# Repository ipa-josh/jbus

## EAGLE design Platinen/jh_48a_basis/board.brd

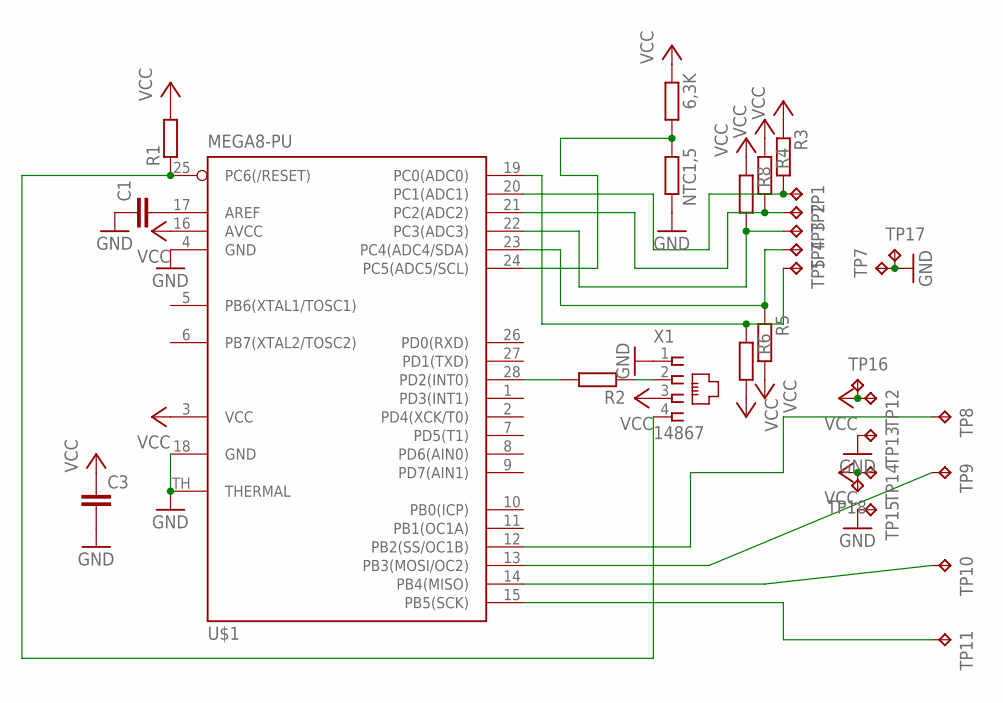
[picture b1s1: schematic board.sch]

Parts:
6,3K: R-EU_R0805; R0805
C1, C3: C-EUC0805; C0805
NTC1,5: R-EU_0207/7; 0207/7
R1, R2, R3, R4, R5, R6, R8: R-EU_R0805; R0805
TP1, TP2, TP3, TP4, TP5, TP7, TP8, TP9, TP10, TP11, TP12, TP13, TP14, TP15, TP16, TP17, TP18: TPPAD1-13; P1-13
U$1: MEGA8-PU; MLF28-TH
X1: 14867

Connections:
GND: C1.1, C3.2, NTC1,5.2, TP7.TP, TP13.TP, TP15.TP, TP17.TP, U$1.4 (GND), U$1.18 (GND), U$1.TH (THERMAL), X1.1
unnamed: R2.2, U$1.28 (PD2(INT0))
unnamed: R1.1, U$1.25 (PC6(/RESET)), X1.4
unnamed: TP8.TP, U$1.12 (PB2(SS/OC1B))
unnamed: TP10.TP, U$1.14 (PB4(MISO))
unnamed: C1.2, U$1.17 (AREF)
unnamed: TP9.TP, U$1.13 (PB3(MOSI/OC2))
unnamed: R8.2, TP3.TP, U$1.22 (PC3(ADC3))
unnamed: R3.2, TP1.TP, U$1.20 (PC1(ADC1))
unnamed: R5.1, TP4.TP, U$1.23 (PC4(ADC4/SDA))
unnamed: R6.1, TP5.TP, U$1.19 (PC0(ADC0))
unnamed: 6,3K.2, NTC1,5.1, U$1.24 (PC5(ADC5/SCL))
unnamed: R2.1, X1.2
unnamed: TP11.TP, U$1.15 (PB5(SCK))
unnamed: R4.2, TP2.TP, U$1.21 (PC2(ADC2))
VCC: 6,3K.1, C3.1, R1.2, R3.1, R4.1, R5.2, R6.2, R8.1, TP12.TP, TP14.TP, TP16.TP, TP18.TP, U$1.3 (VCC), U$1.16 (AVCC), X1.3

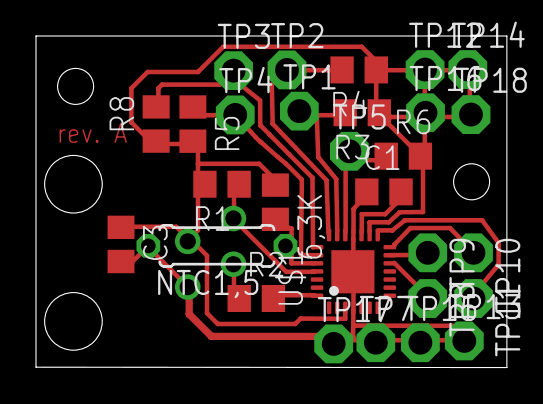
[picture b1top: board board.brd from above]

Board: 2 copper layers, 26.2 x 18.4 mm, 30 parts (1 on the bottom side), 16 nets.

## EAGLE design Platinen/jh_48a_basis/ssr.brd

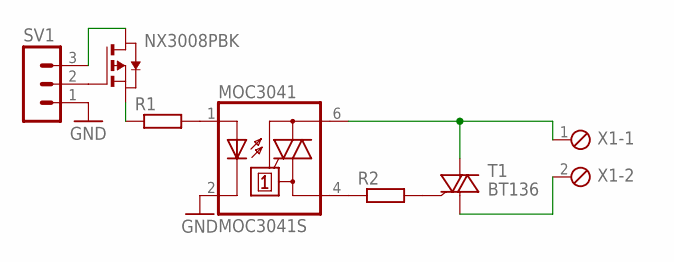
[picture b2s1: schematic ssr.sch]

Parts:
MOC3041: MOC3041S; DIL6-SMD; MPN MOC3041S-M
NX3008PBK: PMOSSOT23; SOT-23
R1, R2: R-EU_R1206; R1206
SV1: MA03-1
T1: BT136; TO220AB
X1: MPT2; 2POL254

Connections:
GND: MOC3041.2 (C), SV1.1
unnamed: MOC3041.1 (A), R1.2
unnamed: NX3008PBK.2 (S), R1.1
unnamed: MOC3041.4 (A1), R2.1
unnamed: R2.2, T1.3 (G)
unnamed: MOC3041.6 (A2), T1.2 (A2), X1.1
unnamed: T1.1 (A1), X1.2
unnamed: NX3008PBK.3 (G), SV1.2
unnamed: NX3008PBK.1 (D), SV1.3

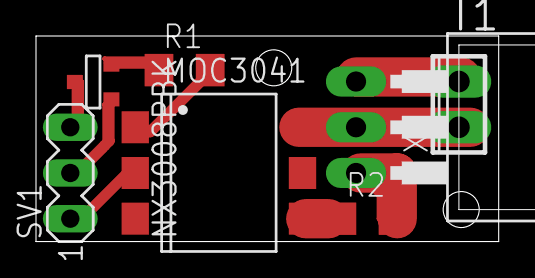
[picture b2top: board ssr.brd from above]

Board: 2 copper layers, 25.7 x 11.4 mm, 7 parts (0 on the bottom side), 9 nets.

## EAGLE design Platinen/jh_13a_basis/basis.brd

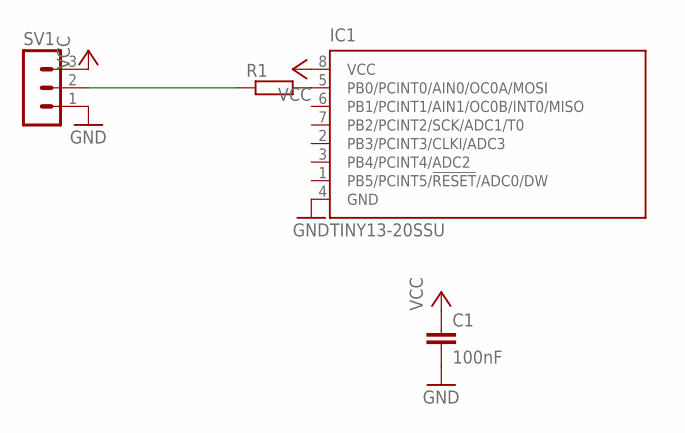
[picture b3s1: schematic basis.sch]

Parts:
C1: 100nF; C0603
IC1: TINY13-20SSU; 8S1
R1: R-EU_R0805; R0805
SV1: MA03-1

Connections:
GND: C1.2, IC1.4 (GND), SV1.1
unnamed: IC1.5 (PB0/PCINT0/AIN0/OC0A/MOSI), R1.2
unnamed: R1.1, SV1.2
VCC: C1.1, IC1.8 (VCC), SV1.3

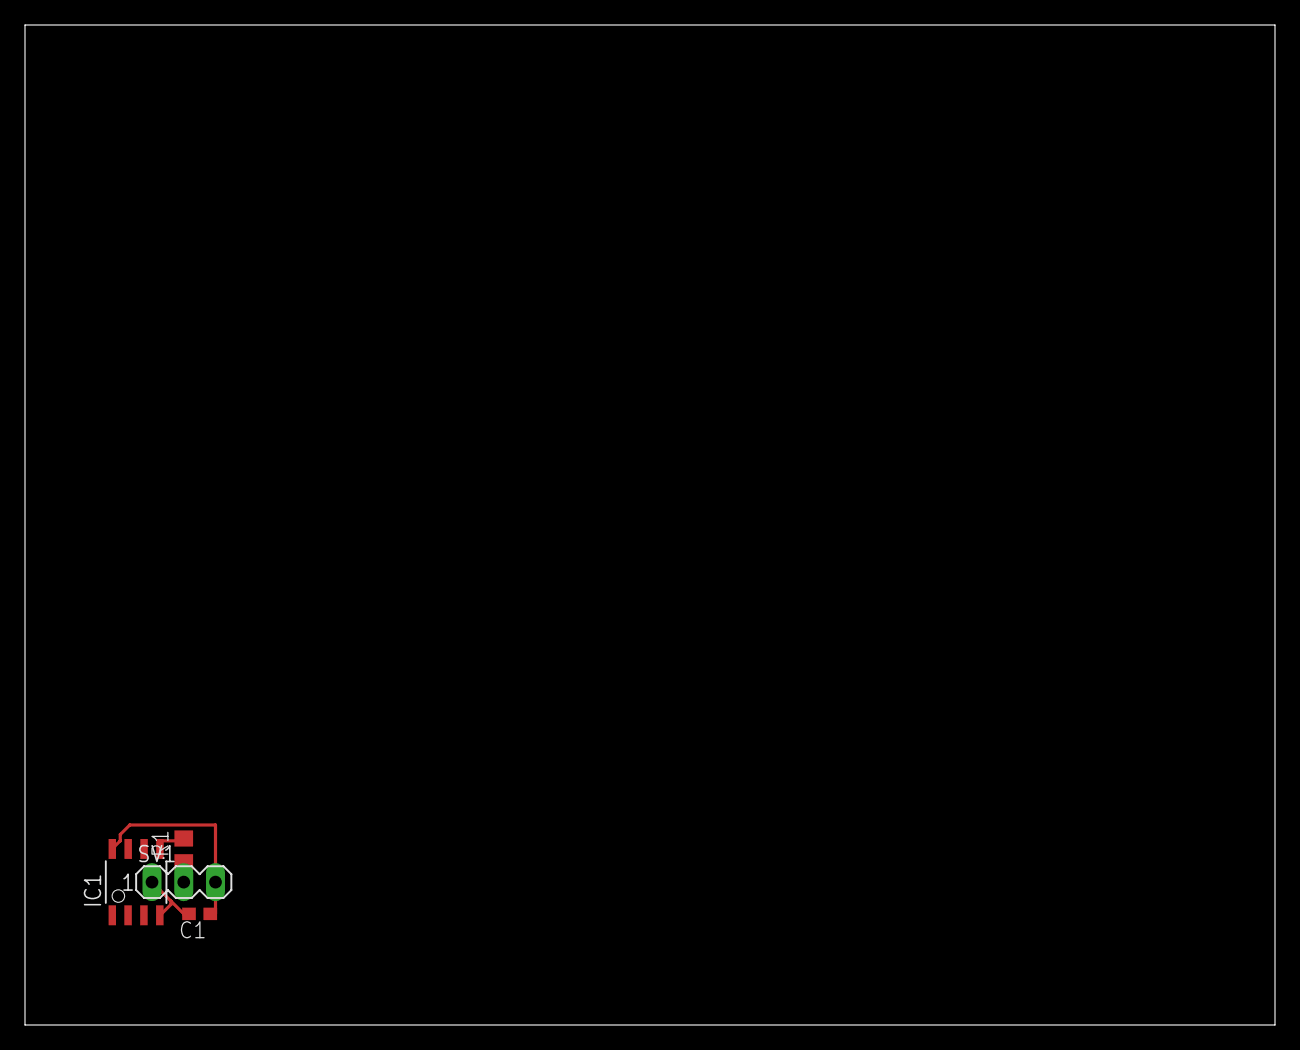
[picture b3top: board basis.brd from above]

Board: 2 copper layers, 100.0 x 80.0 mm, 4 parts (0 on the bottom side), 4 nets.

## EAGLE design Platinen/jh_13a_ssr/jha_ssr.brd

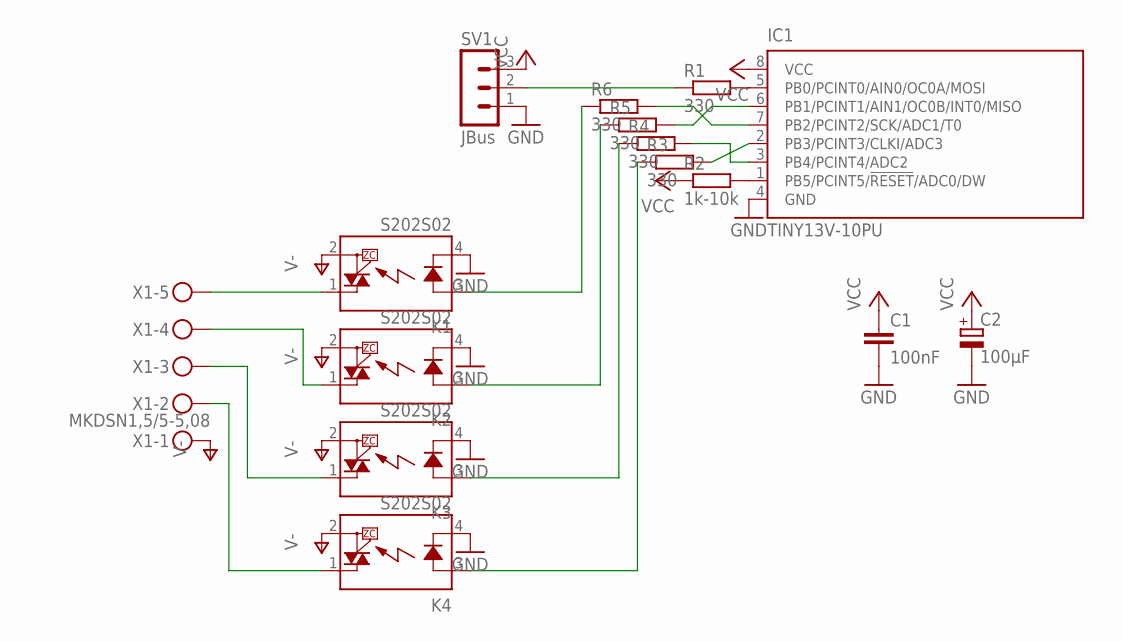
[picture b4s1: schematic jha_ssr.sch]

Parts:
C1: 100nF; C0603
C2: 100µF; E2,5-5
IC1: TINY13V-10PU; DIL08; MPN ATTINY13V-10PU
K1, K2, K3, K4: S202S02
R1, R3, R4, R5, R6: 330; R0805
R2: 1k-10k; R0805
SV1: JBus; MA03-1
X1: MKDSN1,5/5-5,08

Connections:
GND: C1.2, C2.-, IC1.4 (GND), K1.4 (K), K2.4 (K), K3.4 (K), K4.4 (K), SV1.1
unnamed: IC1.5 (PB0/PCINT0/AIN0/OC0A/MOSI), R1.2
unnamed: R1.1, SV1.2
unnamed: IC1.1 (PB5/PCINT5/!RESET!/ADC0/DW), R2.2
unnamed: IC1.3 (PB4/PCINT4/ADC2), R4.2
unnamed: IC1.2 (PB3/PCINT3/CLKI/ADC3), R3.2
unnamed: IC1.6 (PB1/PCINT1/AIN1/OC0B/INT0/MISO), R5.2
unnamed: IC1.7 (PB2/PCINT2/SCK/ADC1/T0), R6.2
unnamed: K1.3 (A), R6.1
unnamed: K2.3 (A), R5.1
unnamed: K3.3 (A), R4.1
unnamed: K4.3 (A), R3.1
unnamed: K4.1 (DS1), X1.2
unnamed: K3.1 (DS1), X1.3
unnamed: K2.1 (DS1), X1.4
unnamed: K1.1 (DS1), X1.5
V-: K1.2 (DS2), K2.2 (DS2), K3.2 (DS2), K4.2 (DS2), X1.1
VCC: C1.1, C2.+, IC1.8 (VCC), R2.1, SV1.3

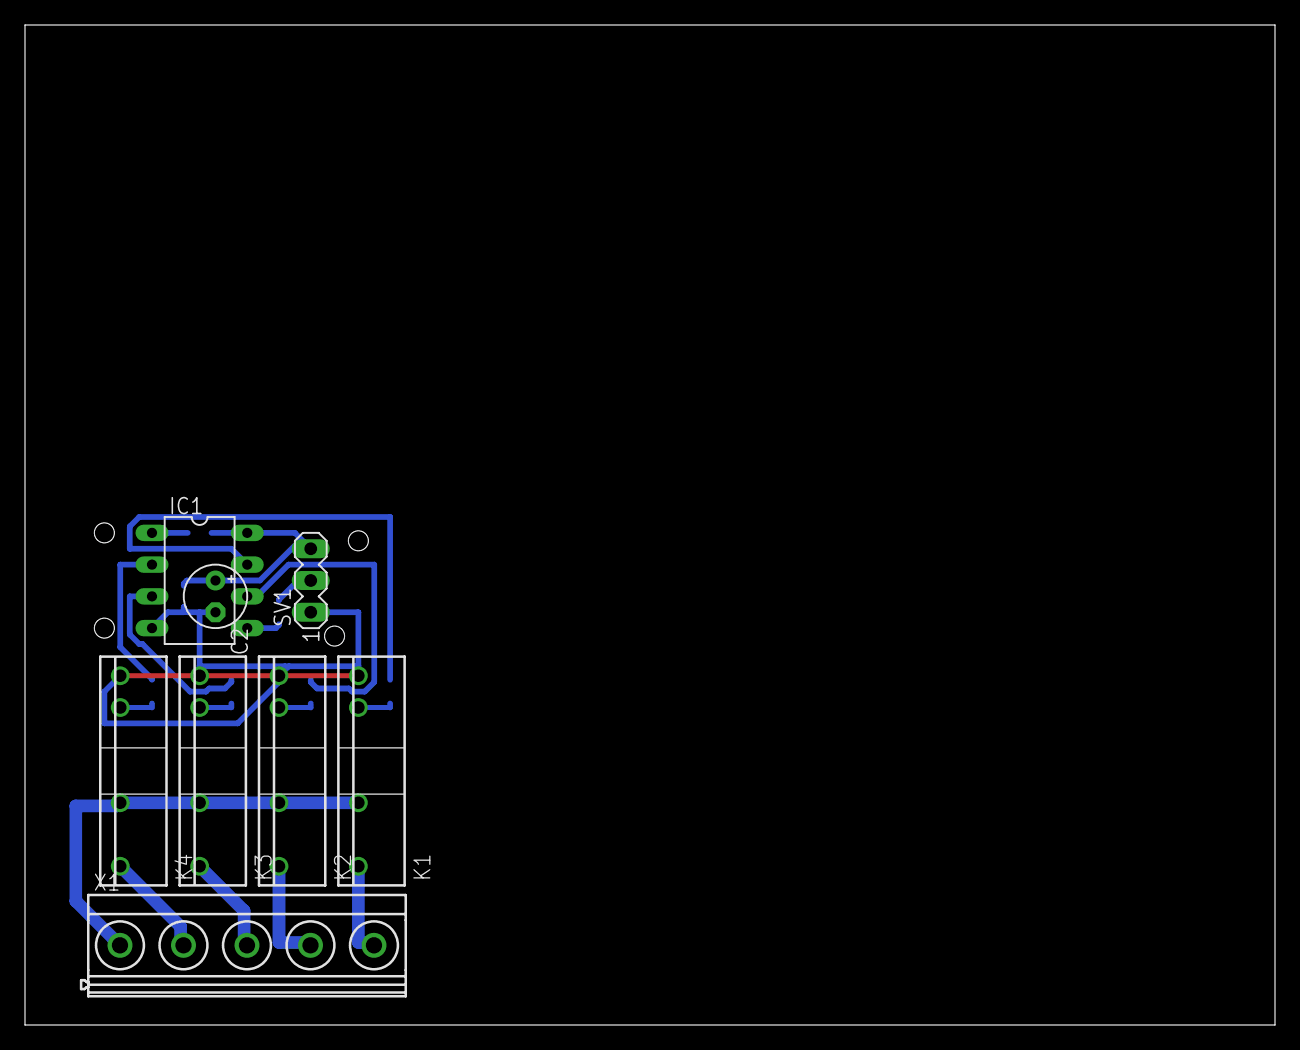
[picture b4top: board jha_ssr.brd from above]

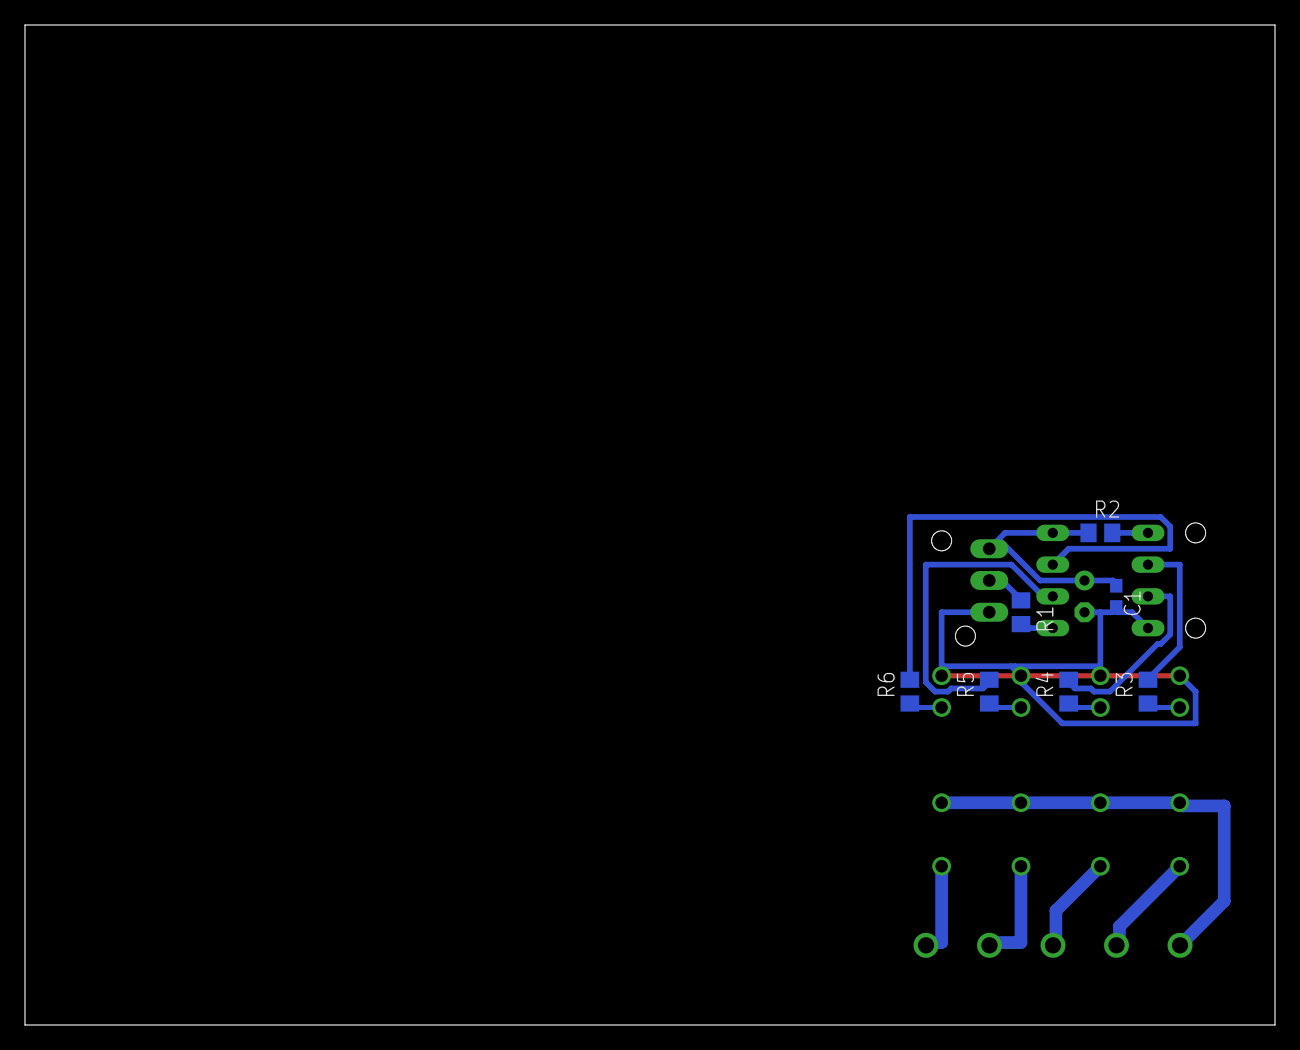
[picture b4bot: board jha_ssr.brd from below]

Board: 2 copper layers, 100.0 x 80.0 mm, 15 parts (7 on the bottom side), 18 nets.

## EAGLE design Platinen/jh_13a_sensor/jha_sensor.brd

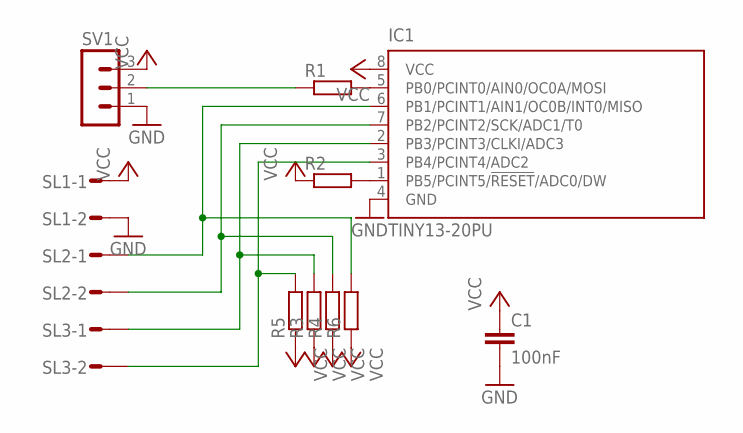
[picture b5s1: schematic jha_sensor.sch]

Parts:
C1: 100nF; C0603
IC1: TINY13-20PU; DIL08; MPN ATTINY13-20PU
R1, R2, R3, R4, R5, R6: R-EU_R0805; R0805
SL1, SL2, SL3: MA02S; 02PA
SV1: MA03-1

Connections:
GND: C1.2, IC1.4 (GND), SL1.2, SV1.1
unnamed: IC1.5 (PB0/PCINT0/AIN0/OC0A/MOSI), R1.2
unnamed: R1.1, SV1.2
unnamed: IC1.1 (PB5/PCINT5/!RESET!/ADC0/DW), R2.2
unnamed: IC1.2 (PB3/PCINT3/CLKI/ADC3), R3.2, SL3.1
unnamed: IC1.7 (PB2/PCINT2/SCK/ADC1/T0), R4.2, SL2.2
unnamed: IC1.6 (PB1/PCINT1/AIN1/OC0B/INT0/MISO), R6.2, SL2.1
unnamed: IC1.3 (PB4/PCINT4/ADC2), R5.2, SL3.2
VCC: C1.1, IC1.8 (VCC), R2.1, R3.1, R4.1, R5.1, R6.1, SL1.1, SV1.3

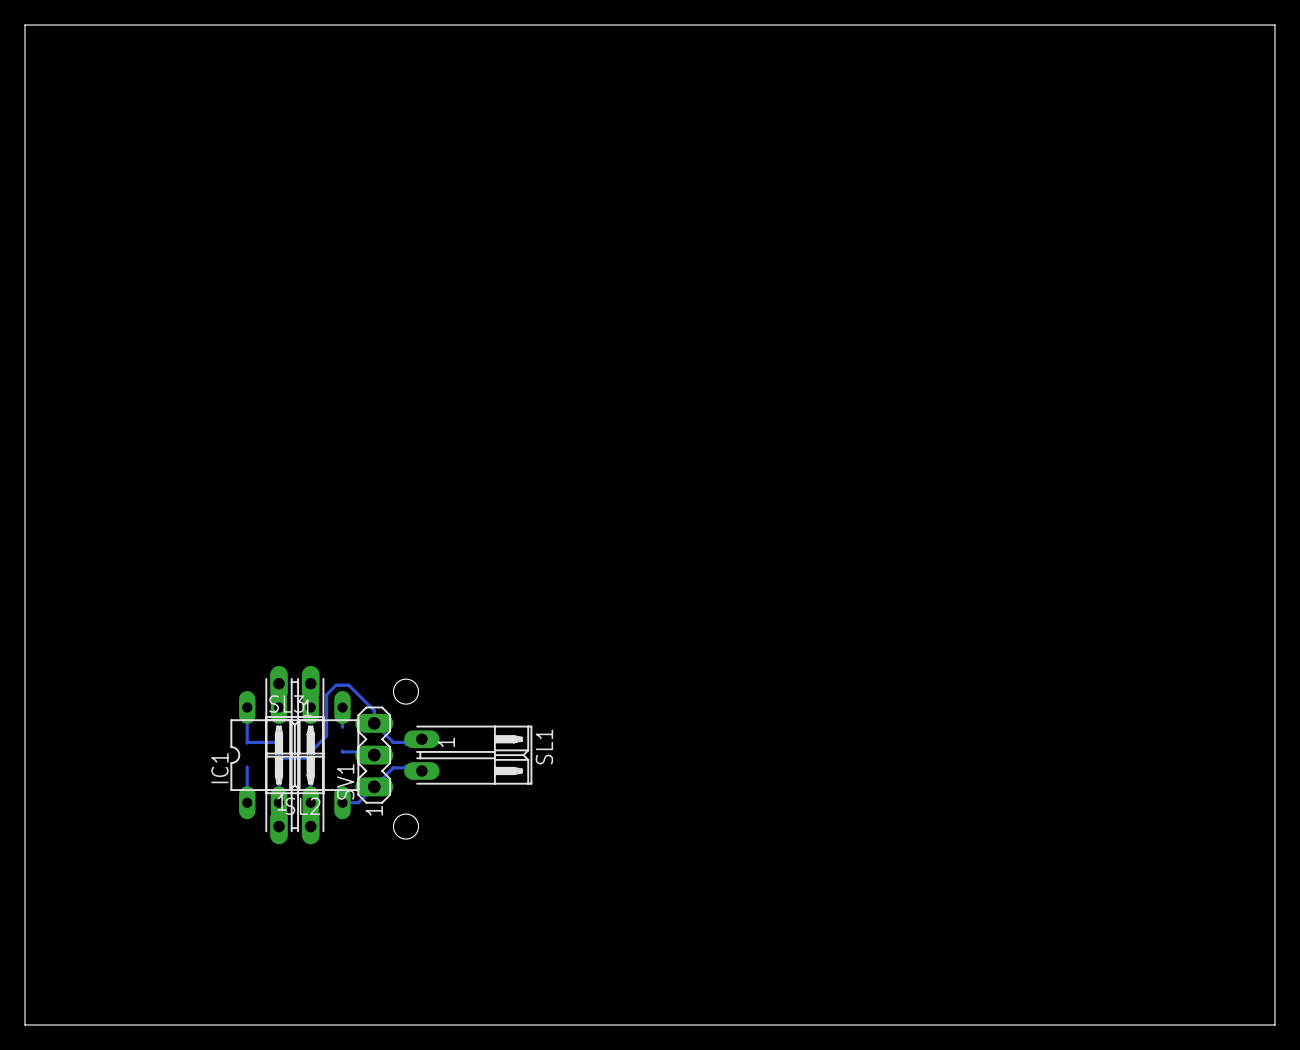
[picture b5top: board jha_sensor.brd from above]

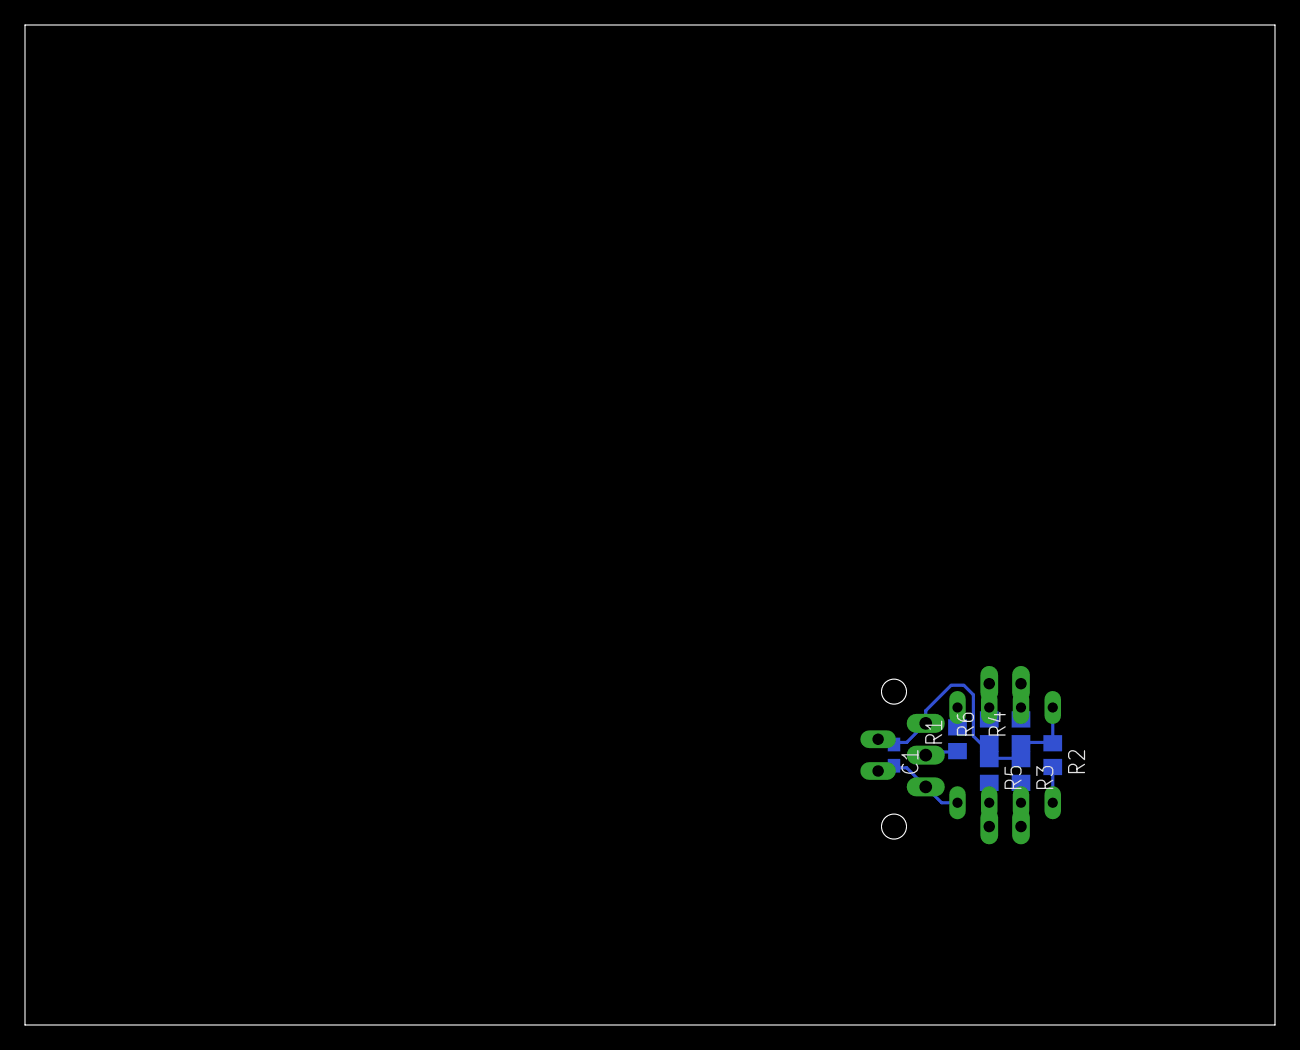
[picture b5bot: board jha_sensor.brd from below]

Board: 2 copper layers, 100.0 x 80.0 mm, 12 parts (7 on the bottom side), 9 nets.

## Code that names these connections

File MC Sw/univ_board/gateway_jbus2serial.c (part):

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	USIDR = 0xFF; // Make sure MSB is '1' before enabling USI_DO.
	USISR = 0xF0 | // Clear all USI interrupt flags.
	0x0F; // Preload the USI counter to generate interrupt at first USI clock.
	DDRB |= (1<<PB1); // Configure USI_DO as output.

	USI_UART_status.ongoing_Transmission_From_Buffer = TRUE;

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// The USI is configured to read data within the pinchange interrupt.
void USI_UART_Initialise_Receiver( void )
{
	PORTB |= (1<<PB1)|(1<<PB0); // Enable pull up on USI DO, DI and SCK pins. (And PB3 because of pin change interrupt)
	DDRB &= ~(1<<PB1)|(1<<PB0); // Set USI DI, DO and SCK pins as inputs.
	USICR = 0; // Disable USI.
	GIFR = (1<<PCIF); // Clear pin change interrupt flag.
	GIMSK |= (1<<PCIE); // Enable pin change interrupt for PB3:0.
	PCMSK |= (1<<PB0);
}

// Puts data in the transmission buffer, after reverseing the bits in the byte.
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// It is here the USI is configured to sample the UART signal.
ISR(SIG_PIN_CHANGE)
{
	if (!( PINB & (1<<PB0) )) // If the USI DI pin is low, then it is likely that it
	{ // was this pin that generated the pin change interrupt.
		TCNT0 = INTERRUPT_STARTUP_DELAY + INITIAL_TIMER0_SEED; // Plant TIMER0 seed to match baudrate (incl interrupt start up time.).
		TCCR0B = (0<<PSR0)|PRESCALER_SETTINGS; // Reset the prescaler and start Timer0.
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		USISR = 0xF0 | // Clear all USI interrupt flags.
		USI_COUNTER_SEED_RECEIVE; // Preload the USI counter to generate interrupt.

		GIMSK &= ~(1<<PCIE); // Disable pin change interrupt for PB3:0.

		USI_UART_status.ongoing_Reception_Of_Package = TRUE;
	}
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				USI_UART_status.ongoing_Transmission_From_Buffer = FALSE;

				TCCR0B = (0<<CS02)|(0<<CS01)|(0<<CS00); // Stop Timer0.
				PORTB |= (1<<PB3)|(1<<PB2)|(1<<PB1)|(1<<PB0); // Enable pull up on USI DO, DI and SCK pins. (And PB3 because of pin change interrupt)
				DDRB &= ~((1<<PB3)|(1<<PB2)|(1<<PB1)|(1<<PB0)); // Set USI DI, DO and SCK pins as inputs.
				USICR = 0; // Disable USI.
				GIFR = (1<<PCIF); // Clear pin change interrupt flag.
				GIMSK |= (1<<PCIE); // Enable pin change interrupt for PB3:0.
			}
		}
	}
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		} // The bit reversing is moved to the application section to save time within the interrupt.

		TCCR0B = (0<<CS02)|(0<<CS01)|(0<<CS00); // Stop Timer0.
		PORTB |= (1<<PB3)|(1<<PB2)|(1<<PB1)|(1<<PB0); // Enable pull up on USI DO, DI and SCK pins. (And PB3 because of pin change interrupt)
		DDRB &= ~((1<<PB3)|(1<<PB2)|(1<<PB1)|(1<<PB0)); // Set USI DI, DO and SCK pins as inputs.
		USICR = 0; // Disable USI.
		GIFR = (1<<PCIF); // Clear pin change interrupt flag.
		GIMSK |= (1<<PCIE); // Enable pin change interrupt for PB3:0.
	}

}
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
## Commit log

2012-11-04 added layout
2012-11-10 ui: init
2012-11-10 layout: init
2012-11-10 layout: update with C
2012-11-10 removed ini files
2012-11-10 server: added history
2012-11-10 server: added default callback and restore function
2012-11-11 ui: autoreload
2012-11-11 server: reboot
2012-11-11 server: restore
2012-11-11 server: interfaces fix
2012-11-11 server: warnings removed
2012-11-11 ui: vis house
2012-11-11 server: start.sh
2012-11-11 server: auth sample file
2012-11-13 ui: added icons
2012-11-13 ui: added error handler
2012-11-13 ui: extended error handler
2012-11-17 server: extended time-path
2012-11-17 added new attribute: error
2012-11-17 ui: added error vis.
2012-11-17 layout: update basis board
2012-11-17 layout: update ssr board
2012-11-17 demo: added sample for AVRNetIO Hw
2012-11-17 demo: added error handle
2012-11-17 demo: added restore delay parameter
2012-11-17 server: delayed restore
2012-11-17 server: bugfix for blocking AvrNetIO
2012-11-17 server: added error handler/rem. blocking
2012-11-17 server: added ts changed sub
2012-11-17 server: getRoot
2012-11-17 server: added ts changed
2012-11-17 server: extension to parse path
2012-11-17 server: delayed history
2012-11-17 ui: fixes for error_handler
2012-11-17 ui: beautifiy
2012-11-17 ui: reconnect
2012-11-17 ui: error
2012-11-17 ui: auto-update
2012-11-17 ui: beautify
2012-11-17 ui: vis: catch error
2012-11-20 ui: added dep
2012-11-20 ui: added editor
2012-11-20 server: moved error to internals
2012-11-20 server: setter for vis.
2012-11-20 server: split up readXML
2012-11-20 server: allow remove el. from HAObject
2012-11-20 server: extra setId for Attr_Error
2012-11-20 server: fix for admin user
2012-11-20 server: beautify
2012-11-20 ui: using local dep.
2012-11-20 ui: added nice scroll
2012-11-20 ui: added new element handler
2012-11-20 ui: cleaning up
2012-11-20 server: extended attr list
2012-11-20 server: moved REBOOT to COMMAND
2012-11-20 server: added new drivers
2012-11-22 ui: added editor handlers
2012-11-22 server: added attr string
2012-12-01 ui: added settings icon
2012-12-09 added sunset
2012-12-09 added jar
2012-12-15 added mc software
2012-12-15 layout: made easier to produce
2012-12-15 server: dependency to uart interface
2012-12-15 server: update to error handling
2012-12-15 server: undo if notify fails
2012-12-15 server: some updates to jbus
2012-12-15 server: added binary
2012-12-15 server: removed reboot.java
2012-12-15 ui: update to editor
2012-12-15 ui: updated css for editor
2012-12-18 added sunset to demo config
2012-12-18 server: added discover
2012-12-18 server: jbus node update
2012-12-18 server: update local attribute
2012-12-18 server: added sub path type for easier handling of derivates
2012-12-18 ui: fix for matching recent changes on paths
2012-12-18 server: update on sunset calc
2012-12-18 ui: added imgs for jbus
2012-12-18 ui: vis. for sunset (not finished)
2012-12-18 server: added jbus hw
2012-12-18 server: added double attr
2012-12-20 removed files
2012-12-20 added mc sw
2012-12-24 server: update binary
2012-12-24 server: removed debug hack
2012-12-24 server: using polling interval
2012-12-24 server: added deps.
2012-12-25 server: update deps for rpi
2012-12-25 server: added INSTALL file
2012-12-25 server: added modified learning method
2012-12-28 mc: fixes
2012-12-28 server: jbus fixes
2012-12-28 mc: little fix
2012-12-28 server: update bin
2012-12-28 new rxtx version
2013-01-12 ui: added vis.
2013-01-12 ui: added edit
2013-01-12 ui: added css
2013-01-12 ui: added deps
2013-01-12 ui: added imgs
2013-01-12 ui: added property sheet for editor
2013-01-12 mc: using OVA and some bug fixes
2013-01-12 server: absolute path deps. to relative
2013-01-12 server: sample auth - added admin for editor
2013-01-12 server: setting pos for timer
2013-01-12 server: sleep before start
2013-01-12 server: added history intf.
2013-01-12 server: editor with activation timeout and image list
2013-01-12 server: changed jbus interface
2013-01-12 server: added reboot
2013-01-12 server: jbus working
2013-01-12 server: minor fixes for sunset
2013-01-12 server: extended changed ts for attributes
2013-01-12 server: made new features public
2013-01-12 server: moved to new connection lib
2013-01-12 server: optimized notifier
2013-01-12 server: fixes to atomic attributes
2013-01-12 server: sqlite allows now queries
2013-01-12 server: getter for attribute conversion
2013-01-12 server: added missing groupt for admin
2013-01-12 server: escaping string for json
2013-01-12 server: decoding url
2013-01-12 server: removed warnings
2013-01-12 ui: added property sheet
2013-01-12 ui: added list_images to editor
2013-01-12 ui: minor fix
2013-01-12 ui: added history
2013-01-12 ui: cleaning
2013-01-12 ui: absolute path to ui element
2013-01-12 ui: added url encoding
2013-01-12 ui: some changes
2013-01-12 ui: removed file
2013-01-12 ui: changes
2013-01-12 server: added dp jollyday
2013-01-12 server: removed debug output
2013-01-12 server: fixed id settings
2013-01-12 server: added delay
2013-01-12 server: fixed id
2013-01-12 server: fixed sql query
2013-01-12 ui: fixed js setter
2013-01-12 ui: updated history time interval to 30min
2013-01-12 added lightning
2013-01-12 ui: update to color
2013-01-13 ui: update to ligthning
2013-01-13 server: start script for linux updated
2013-05-22 added weka for classification
2013-05-22 update to responsive split layout
2013-05-28 mc: fixed flag bug
2013-05-28 sw: beautify
2013-05-28 sw: check for lost devices
2013-05-28 sw: last received
2013-05-28 sw: conversion double
2013-05-28 sw: index for history
2013-05-28 sw: error handling
2013-05-28 added missing files
2013-05-28 mc: config
2013-05-28 mc: added rollo
2015-03-14 Migrating wiki contents from Google Code
